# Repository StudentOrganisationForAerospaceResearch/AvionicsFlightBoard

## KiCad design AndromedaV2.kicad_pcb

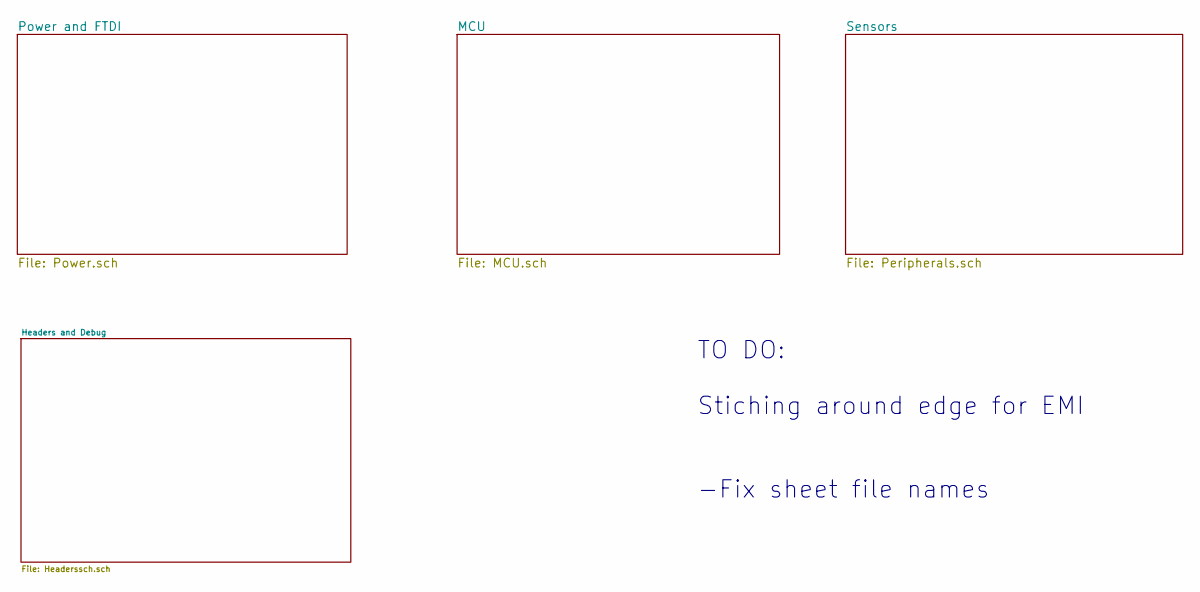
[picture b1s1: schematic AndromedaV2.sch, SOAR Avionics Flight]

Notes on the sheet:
TO DO: Stiching around edge for EMI -Fix sheet file names

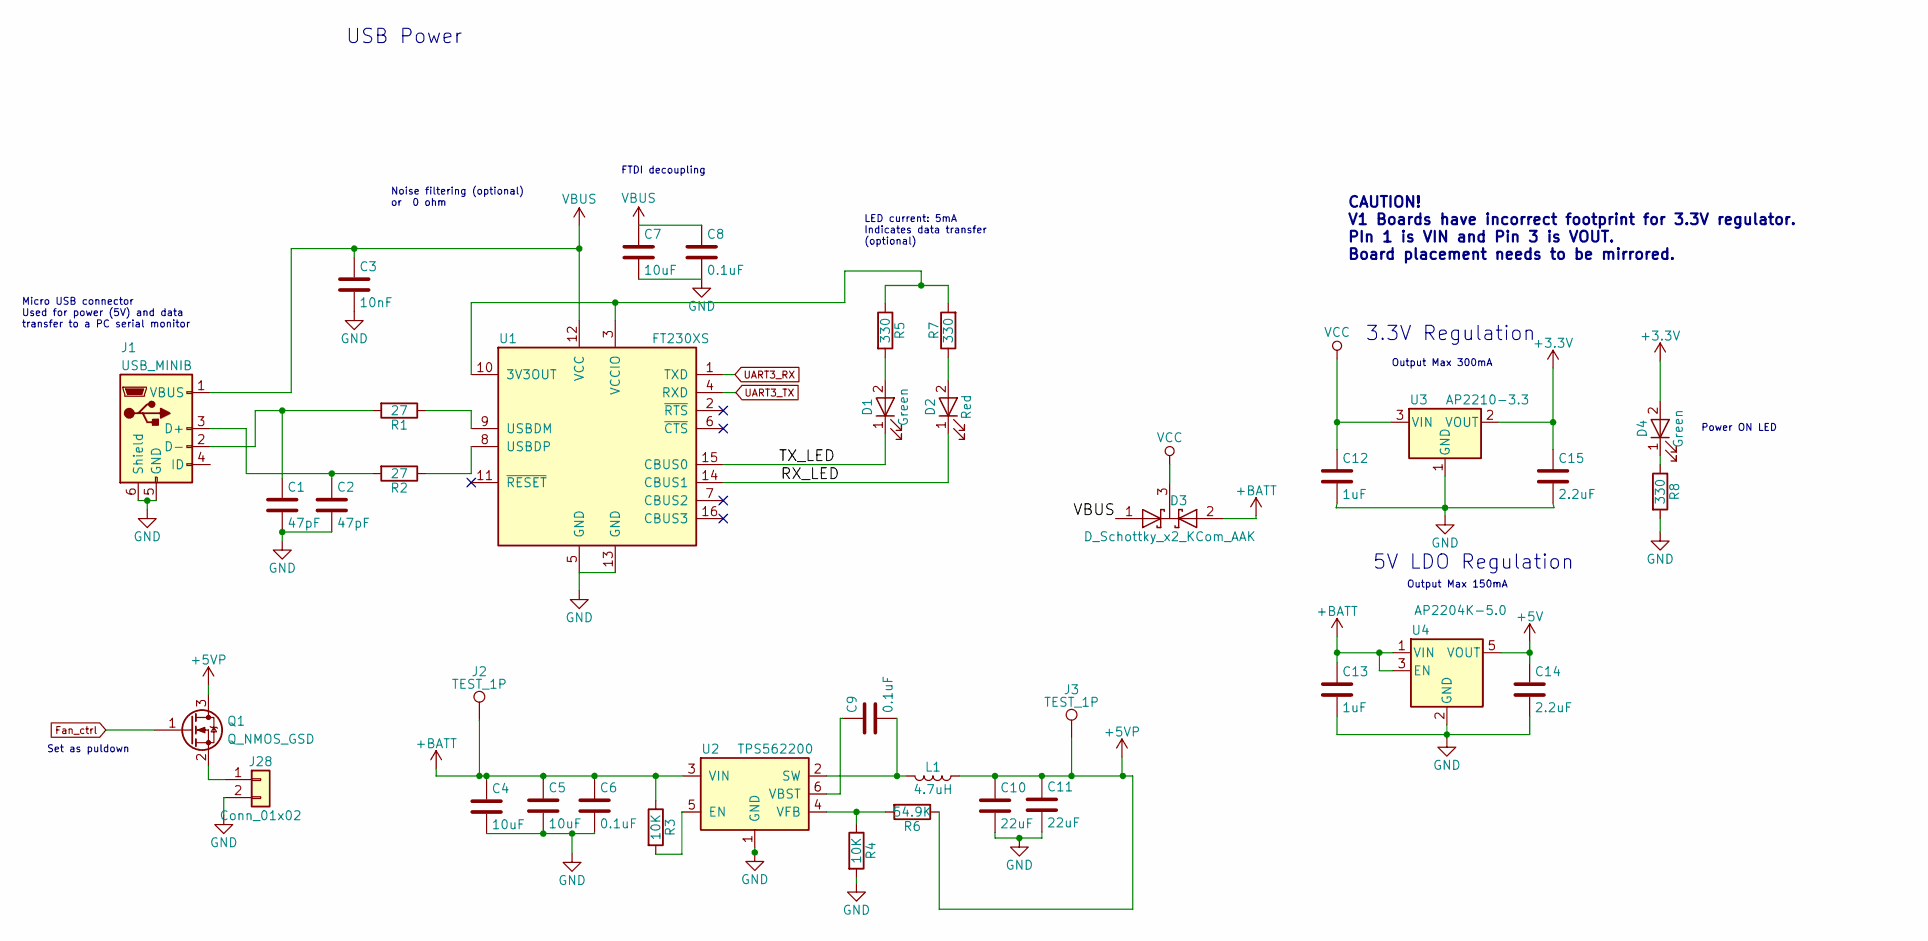
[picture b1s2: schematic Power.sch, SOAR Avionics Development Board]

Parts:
C1, C2: 47pF; C_0603
C3: 10nF; C_0603
C4, C5, C7: 10uF; C_0603
C6, C8, C9: 0.1uF; C_0603
C10, C11: 22uF; C_0603
C12, C13: 1uF; C_0603
C14, C15: 2.2uF; C_0603
D1, D4: Green; LED_0805_2012Metric; Digikey LG R971-KN-1
D2: Red; LED_0805_2012Metric; Digikey 475-1278-1-ND
D3: D_Schottky_x2_KCom_AAK; SOT-23; Digikey 1727-5188-1-ND
J1: USB_MINIB; USB-Mini-B; Digikey 690-005-299-043
J2, J3: TEST_1P; Test_Point_Pad_d1.5mm
J28: Conn_01x02; TerminalBlock_5mm_2POS_ED2600
L1: 4.7uH; L_1008
Q1: Q_NMOS_GSD; SOT-23
R1, R2: 27; R_0603
R3, R4: 10K; R_0603
R5, R7, R8: 330; R_0603
R6: 54.9K; R_0603
U1: FT230XS; SSOP-16_3.9x4.9mm_P0.635mm; Digikey 768-1135-1-ND
U2: TPS562200; SOT-23-6
U3: AP2210-3.3; SOT-23
U4: AP2204K-5.0; SOT-23-5

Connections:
+3V3: C15.1, D4.2 (A), U3.2 (VOUT); also elsewhere on the board
+5V: C14.1, U4.5 (VOUT); also elsewhere on the board
+5VP: C10.1, C11.1, J3.1, L1.1, Q1.3 (D), R6.1; also elsewhere on the board
+BATT: C4.1, C5.1, C6.1, C13.1, D3.2 (A), J2.1, R3.1, U2.3 (VIN), U4.1 (VIN), U4.3 (EN); also elsewhere on the board
/Power and FTDI/RX_LED: D2.1 (K), U1.14 (CBUS1)
/Power and FTDI/TX_LED: D1.1 (K), U1.15 (CBUS0)
Fan_ctrl: Q1.1 (G); also elsewhere on the board
GND: C1.2, C2.2, C3.2, C4.2, C5.2, C6.2, C7.2, C8.2, C10.2, C11.2, C12.2, C13.2, C14.2, C15.2, J1.5 (GND), J1.6 (Shield), J28.2, R4.2, R8.2, U1.5 (GND), U1.13 (GND), U2.1 (GND), U3.1 (GND), U4.2 (GND); also elsewhere on the board
unnamed: C1.1, J1.2 (D-), R1.2
unnamed: C2.1, J1.3 (D+), R2.2
unnamed: C9.1, U2.6 (VBST)
unnamed: C9.2, L1.2, U2.2 (SW)
unnamed: D1.2 (A), R5.2
unnamed: D2.2 (A), R7.1
unnamed: D4.1 (K), R8.1
unnamed: J28.1, Q1.2 (S)
unnamed: R1.1, U1.9 (USBDM)
unnamed: R2.1, U1.8 (USBDP)
unnamed: R3.2, U2.5 (EN)
unnamed: R4.1, R6.2, U2.4 (VFB)
unnamed: R5.1, R7.2
unnamed: U1.3 (VCCIO), U1.10 (3V3OUT)
UART3_RX: U1.1 (TXD); also elsewhere on the board
UART3_TX: U1.4 (RXD); also elsewhere on the board
VBUS: C3.1, C7.1, C8.1, D3.1 (A), J1.1 (VBUS), U1.12 (VCC)
VCC: C12.1, D3.3 (K), U3.3 (VIN)

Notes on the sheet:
Output Max 300mA
Power ON LED
LED current: 5mA Indicates data transfer (optional)
Micro USB connector Used for power (5V) and data transfer to a PC serial monitor
Noise filtering (optional) or 0 ohm
FTDI decoupling
USB Power
3.3V Regulation
5V LDO Regulation
CAUTION! V1 Boards have incorrect footprint for 3.3V regulator. PIn 1 is VIN and Pin 3 is VOUT. Board placement needs to be mirrored.
Output Max 150mA
Set as puldown

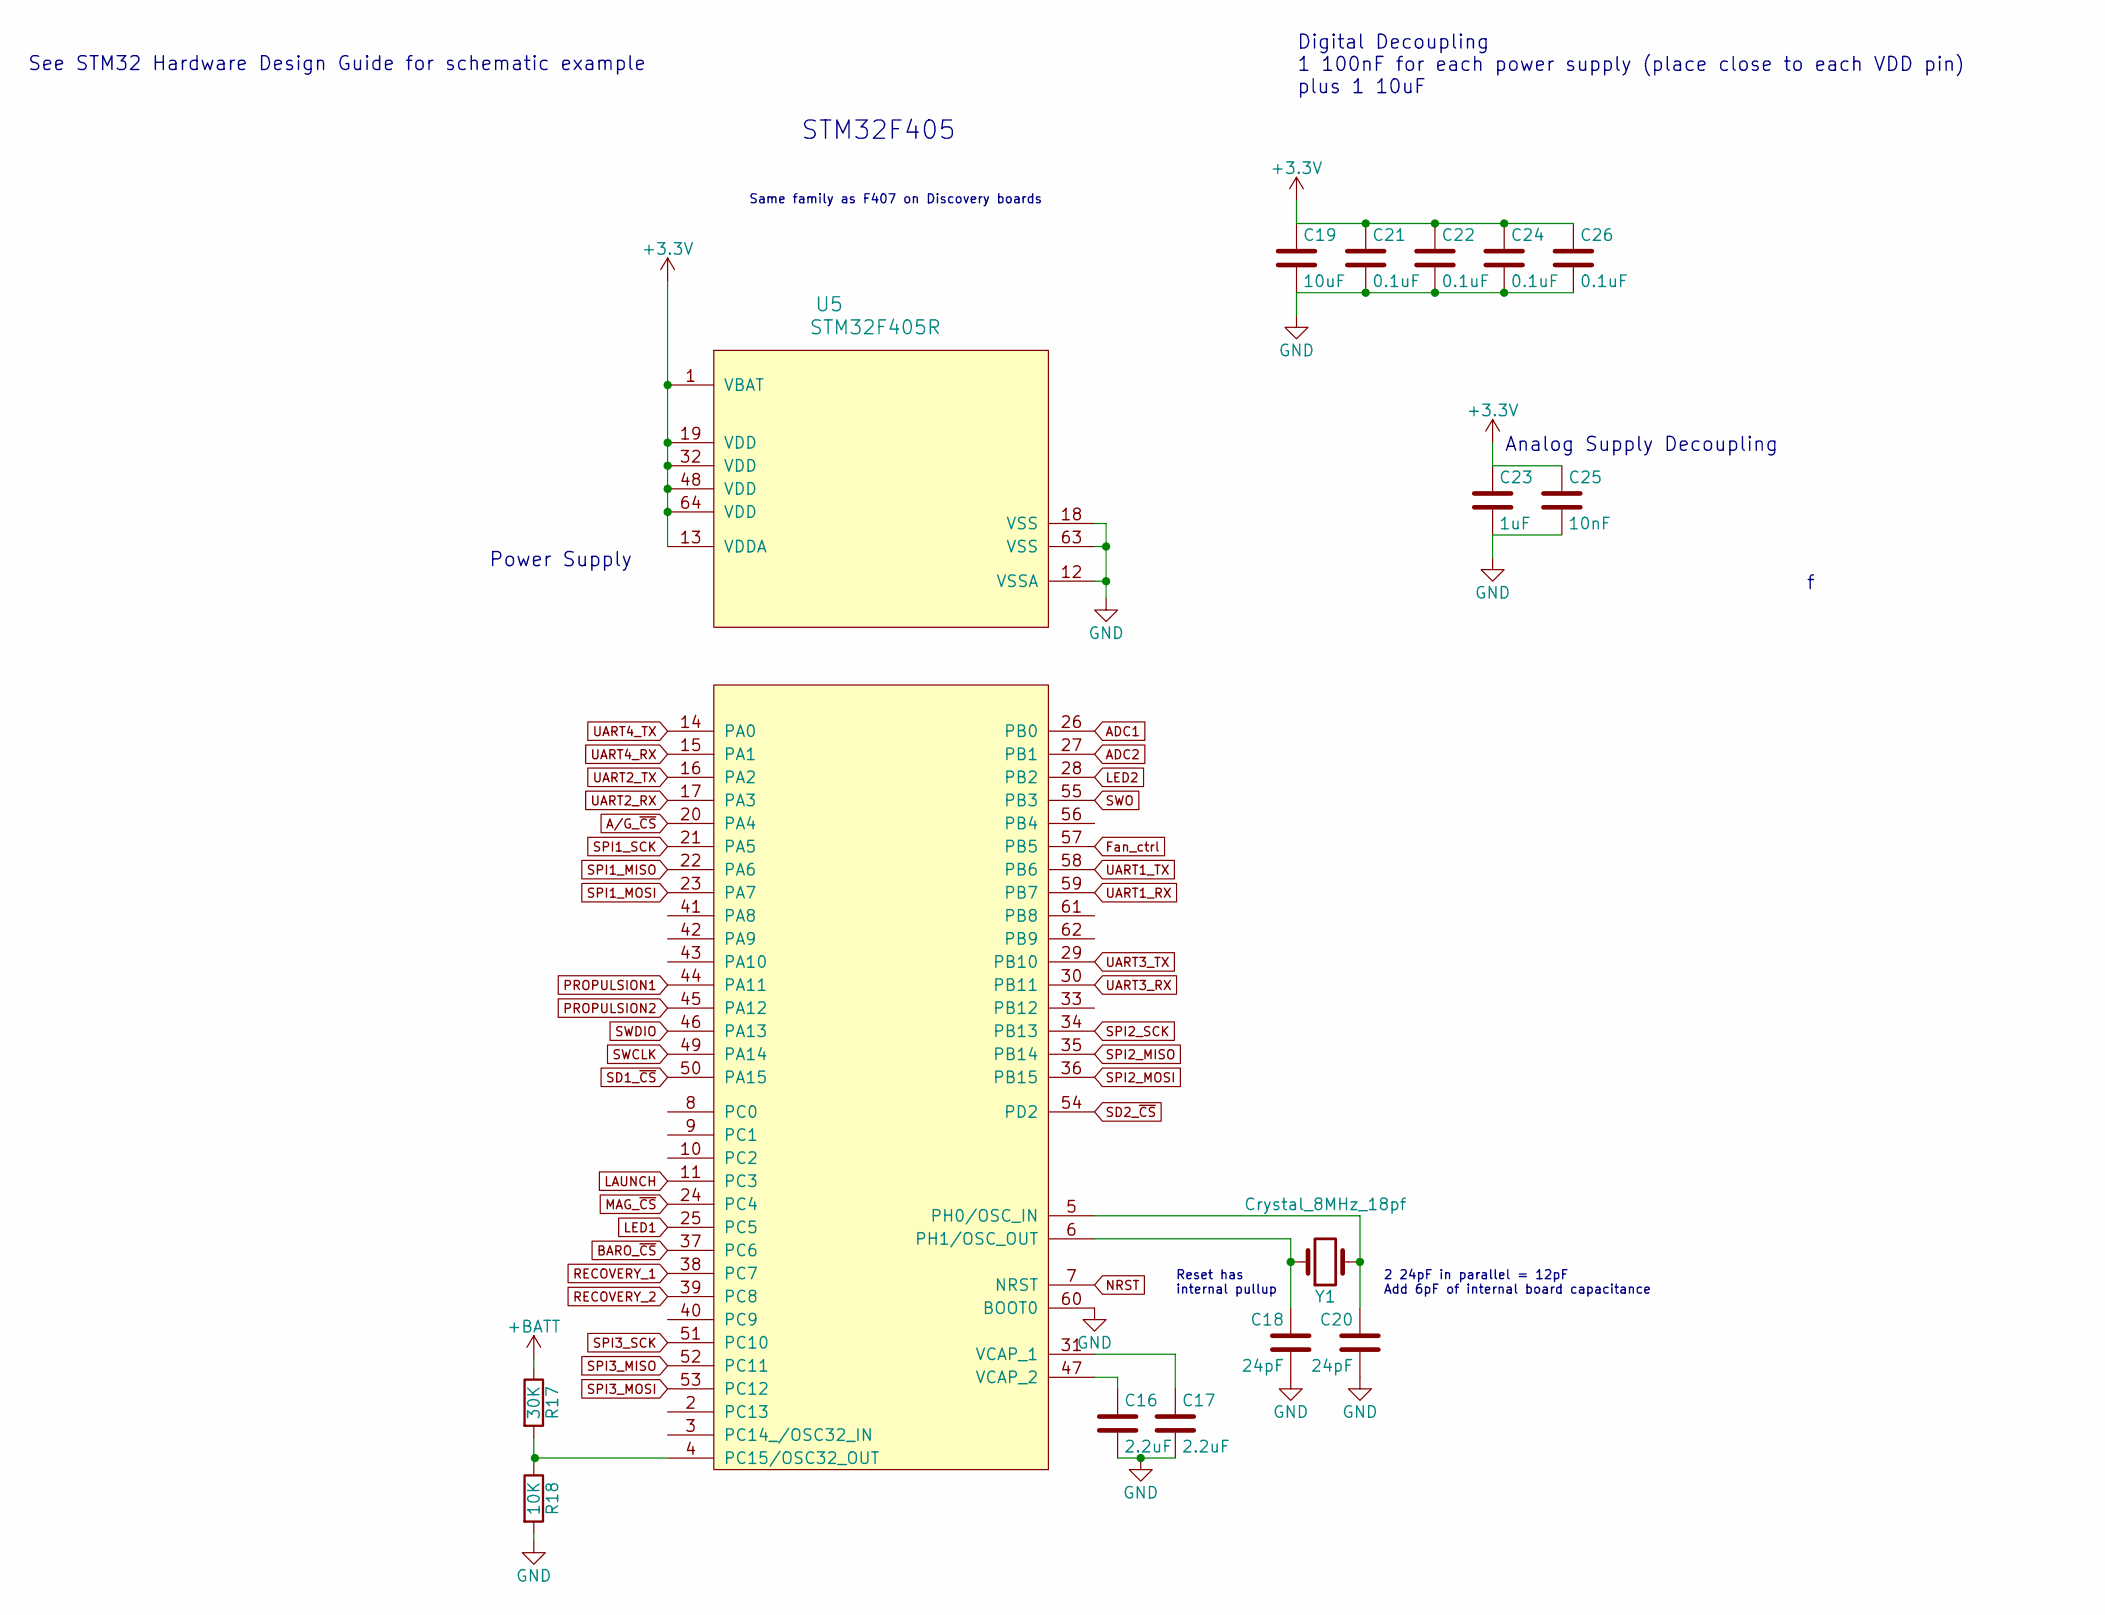
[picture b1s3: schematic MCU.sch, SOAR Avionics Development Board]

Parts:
C16, C17: 2.2uF; C_0603
C18, C20: 24pF; C_0603
C19: 10uF; C_0603
C21, C22, C24, C26: 0.1uF; C_0603
C23: 1uF; C_0603
C25: 10nF; C_0603
R17: 30K; R_0603
R18: 10K; R_0603
U5: STM32F405R; LQFP-64_10x10mm_P0.5mm; Digikey 497-11767-ND
Y1: Crystal_8MHz_18pf; Crystal_SMD_HC49-SD; Digikey 535-9089-1-ND

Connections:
+3V3: C19.1, C21.1, C22.1, C23.1, C24.1, C25.1, C26.1, U5.1 (VBAT), U5.13 (VDDA), U5.19 (VDD), U5.32 (VDD), U5.48 (VDD), U5.64 (VDD); also elsewhere on the board
+BATT: R17.1; also elsewhere on the board
A/G_~CS: U5.20 (PA4); also elsewhere on the board
ADC1: U5.26 (PB0); also elsewhere on the board
ADC2: U5.27 (PB1); also elsewhere on the board
BARO_~CS: U5.37 (PC6); also elsewhere on the board
Fan_ctrl: U5.57 (PB5); also elsewhere on the board
GND: C16.2, C17.2, C18.2, C19.2, C20.2, C21.2, C22.2, C23.2, C24.2, C25.2, C26.2, R18.2, U5.12 (VSSA), U5.18 (VSS), U5.60 (BOOT0), U5.63 (VSS); also elsewhere on the board
LAUNCH: U5.11 (PC3); also elsewhere on the board
LED1: U5.25 (PC5); also elsewhere on the board
LED2: U5.28 (PB2); also elsewhere on the board
MAG_~CS: U5.24 (PC4); also elsewhere on the board
NRST: U5.7 (NRST); also elsewhere on the board
unnamed: C16.1, U5.47 (VCAP_2)
unnamed: C17.1, U5.31 (VCAP_1)
unnamed: C18.1, U5.6 (PH1/OSC_OUT), Y1.1
unnamed: C20.1, U5.5 (PH0/OSC_IN), Y1.2
unnamed: R17.2, R18.1, U5.4 (PC15/OSC32_OUT)
PROPULSION1: U5.44 (PA11); also elsewhere on the board
PROPULSION2: U5.45 (PA12); also elsewhere on the board
RECOVERY_1: U5.38 (PC7); also elsewhere on the board
RECOVERY_2: U5.39 (PC8); also elsewhere on the board
SD1_~CS: U5.50 (PA15); also elsewhere on the board
SD2_~CS: U5.54 (PD2); also elsewhere on the board
SPI1_MISO: U5.22 (PA6); also elsewhere on the board
SPI1_MOSI: U5.23 (PA7); also elsewhere on the board
SPI1_SCK: U5.21 (PA5); also elsewhere on the board
SPI2_MISO: U5.35 (PB14); also elsewhere on the board
SPI2_MOSI: U5.36 (PB15); also elsewhere on the board
SPI2_SCK: U5.34 (PB13); also elsewhere on the board
SPI3_MISO: U5.52 (PC11); also elsewhere on the board
SPI3_MOSI: U5.53 (PC12); also elsewhere on the board
SPI3_SCK: U5.51 (PC10); also elsewhere on the board
SWCLK: U5.49 (PA14); also elsewhere on the board
SWDIO: U5.46 (PA13); also elsewhere on the board
SWO: U5.55 (PB3); also elsewhere on the board
UART1_RX: U5.59 (PB7); also elsewhere on the board
UART1_TX: U5.58 (PB6); also elsewhere on the board
UART2_RX: U5.17 (PA3); also elsewhere on the board
UART2_TX: U5.16 (PA2); also elsewhere on the board
UART3_RX: U5.30 (PB11); also elsewhere on the board
UART3_TX: U5.29 (PB10); also elsewhere on the board
UART4_RX: U5.15 (PA1); also elsewhere on the board
UART4_TX: U5.14 (PA0); also elsewhere on the board

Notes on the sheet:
Reset has internal pullup
Digital Decoupling 1 100nF for each power supply (place close to each VDD pin) plus 1 10uF
Analog Supply Decoupling
See STM32 Hardware Design Guide for schematic example
Power Supply
2 24pF in parallel = 12pF Add 6pF of internal board capacitance
STM32F405
Same family as F407 on Discovery boards

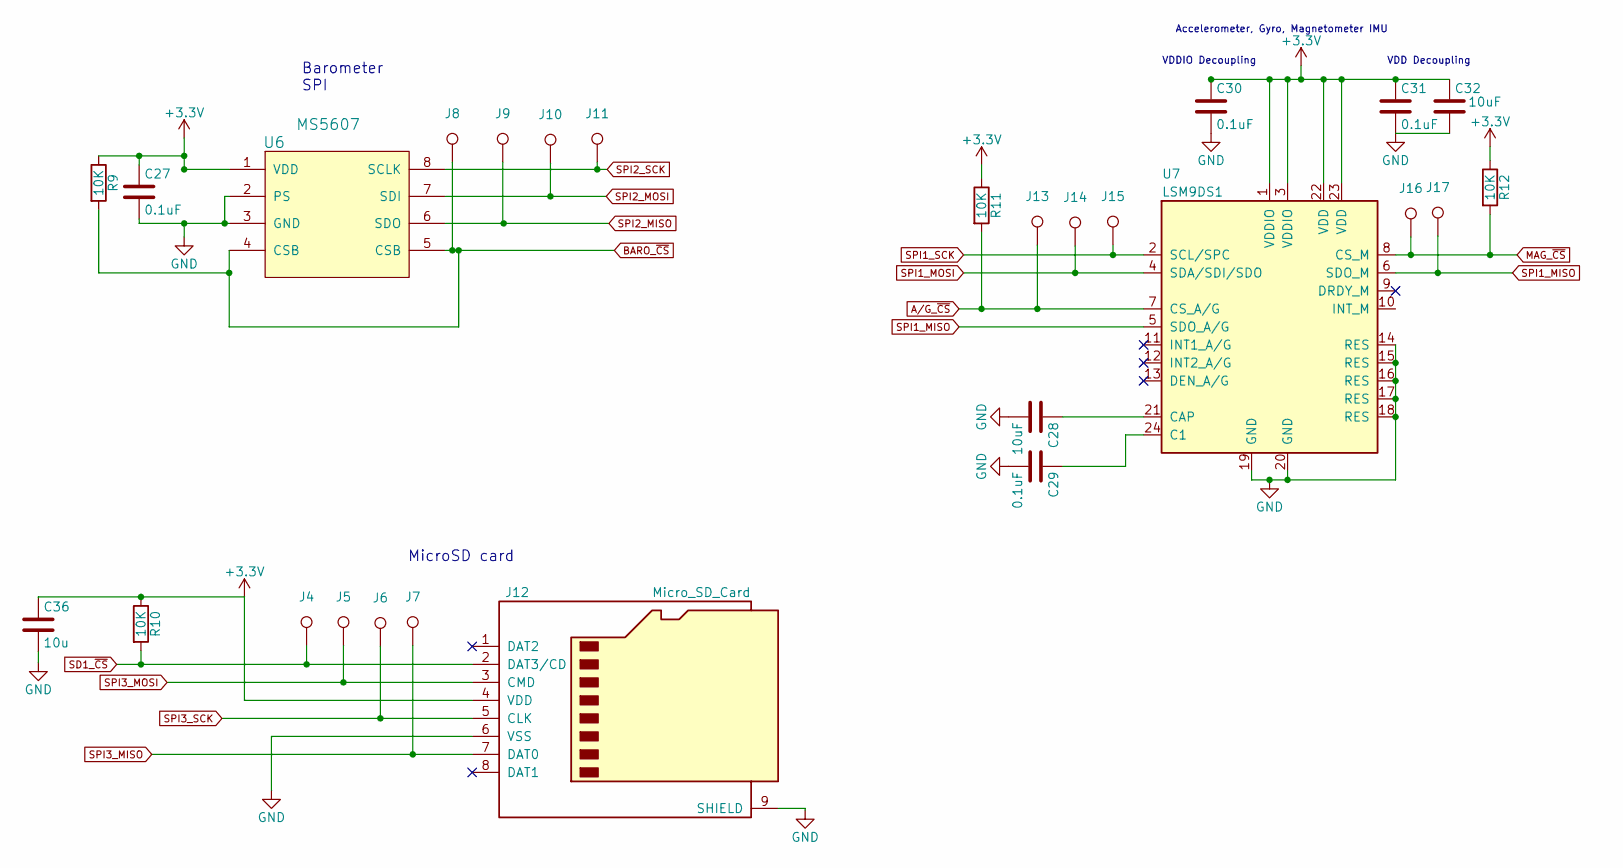
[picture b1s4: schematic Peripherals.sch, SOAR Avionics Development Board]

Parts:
C27, C29, C30, C31: 0.1uF; C_0603
C28, C32: 10uF; C_0603
C36: 10u; C_0603
J4, J5, J6, J7, J8, J9, J10, J11, J13, J14, J15, J16, J17: TEST_1P; Test_Point_Pad_d1.5mm
J12: Micro_SD_Card; Conn,Molex,Hinged_microSD; Digikey 0472192001
R9, R10, R11, R12: 10K; R_0603
U6: MS5607; LGA-8_3x5mm_P1.25mm; Digikey MS560702BA03-00
U7: LSM9DS1; LGA-24L_3x3.5mm_P0.43mm; Digikey 497-14946-1-ND

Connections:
+3V3: C27.1, C30.1, C31.1, C32.1, C36.1, J12.4 (VDD), R9.1, R10.1, R11.1, R12.1, U6.1 (VDD), U7.1 (VDDIO), U7.3 (VDDIO), U7.22 (VDD), U7.23 (VDD); also elsewhere on the board
A/G_~CS: J13.1, R11.2, U7.7 (CS_A/G); also elsewhere on the board
BARO_~CS: J8.1, R9.2, U6.4 (CSB), U6.5 (CSB); also elsewhere on the board
GND: C27.2, C28.2, C29.2, C30.2, C31.2, C32.2, C36.2, J12.6 (VSS), J12.9 (SHIELD), U6.2 (PS), U6.3 (GND), U7.14 (RES), U7.15 (RES), U7.16 (RES), U7.17 (RES), U7.18 (RES), U7.19 (GND), U7.20 (GND); also elsewhere on the board
MAG_~CS: J16.1, R12.2, U7.8 (CS_M); also elsewhere on the board
unnamed: C28.1, U7.21 (CAP)
unnamed: C29.1, U7.24 (C1)
SD1_~CS: J4.1, J12.2 (DAT3/CD), R10.2; also elsewhere on the board
SPI1_MISO: J17.1, U7.5 (SDO_A/G), U7.6 (SDO_M); also elsewhere on the board
SPI1_MOSI: J14.1, U7.4 (SDA/SDI/SDO); also elsewhere on the board
SPI1_SCK: J15.1, U7.2 (SCL/SPC); also elsewhere on the board
SPI2_MISO: J9.1, U6.6 (SDO); also elsewhere on the board
SPI2_MOSI: J10.1, U6.7 (SDI); also elsewhere on the board
SPI2_SCK: J11.1, U6.8 (SCLK); also elsewhere on the board
SPI3_MISO: J7.1, J12.7 (DAT0); also elsewhere on the board
SPI3_MOSI: J5.1, J12.3 (CMD); also elsewhere on the board
SPI3_SCK: J6.1, J12.5 (CLK); also elsewhere on the board

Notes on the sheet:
Barometer SPI
VDD Decoupling
VDDIO Decoupling
MicroSD card
Accelerometer, Gyro, Magnetometer IMU

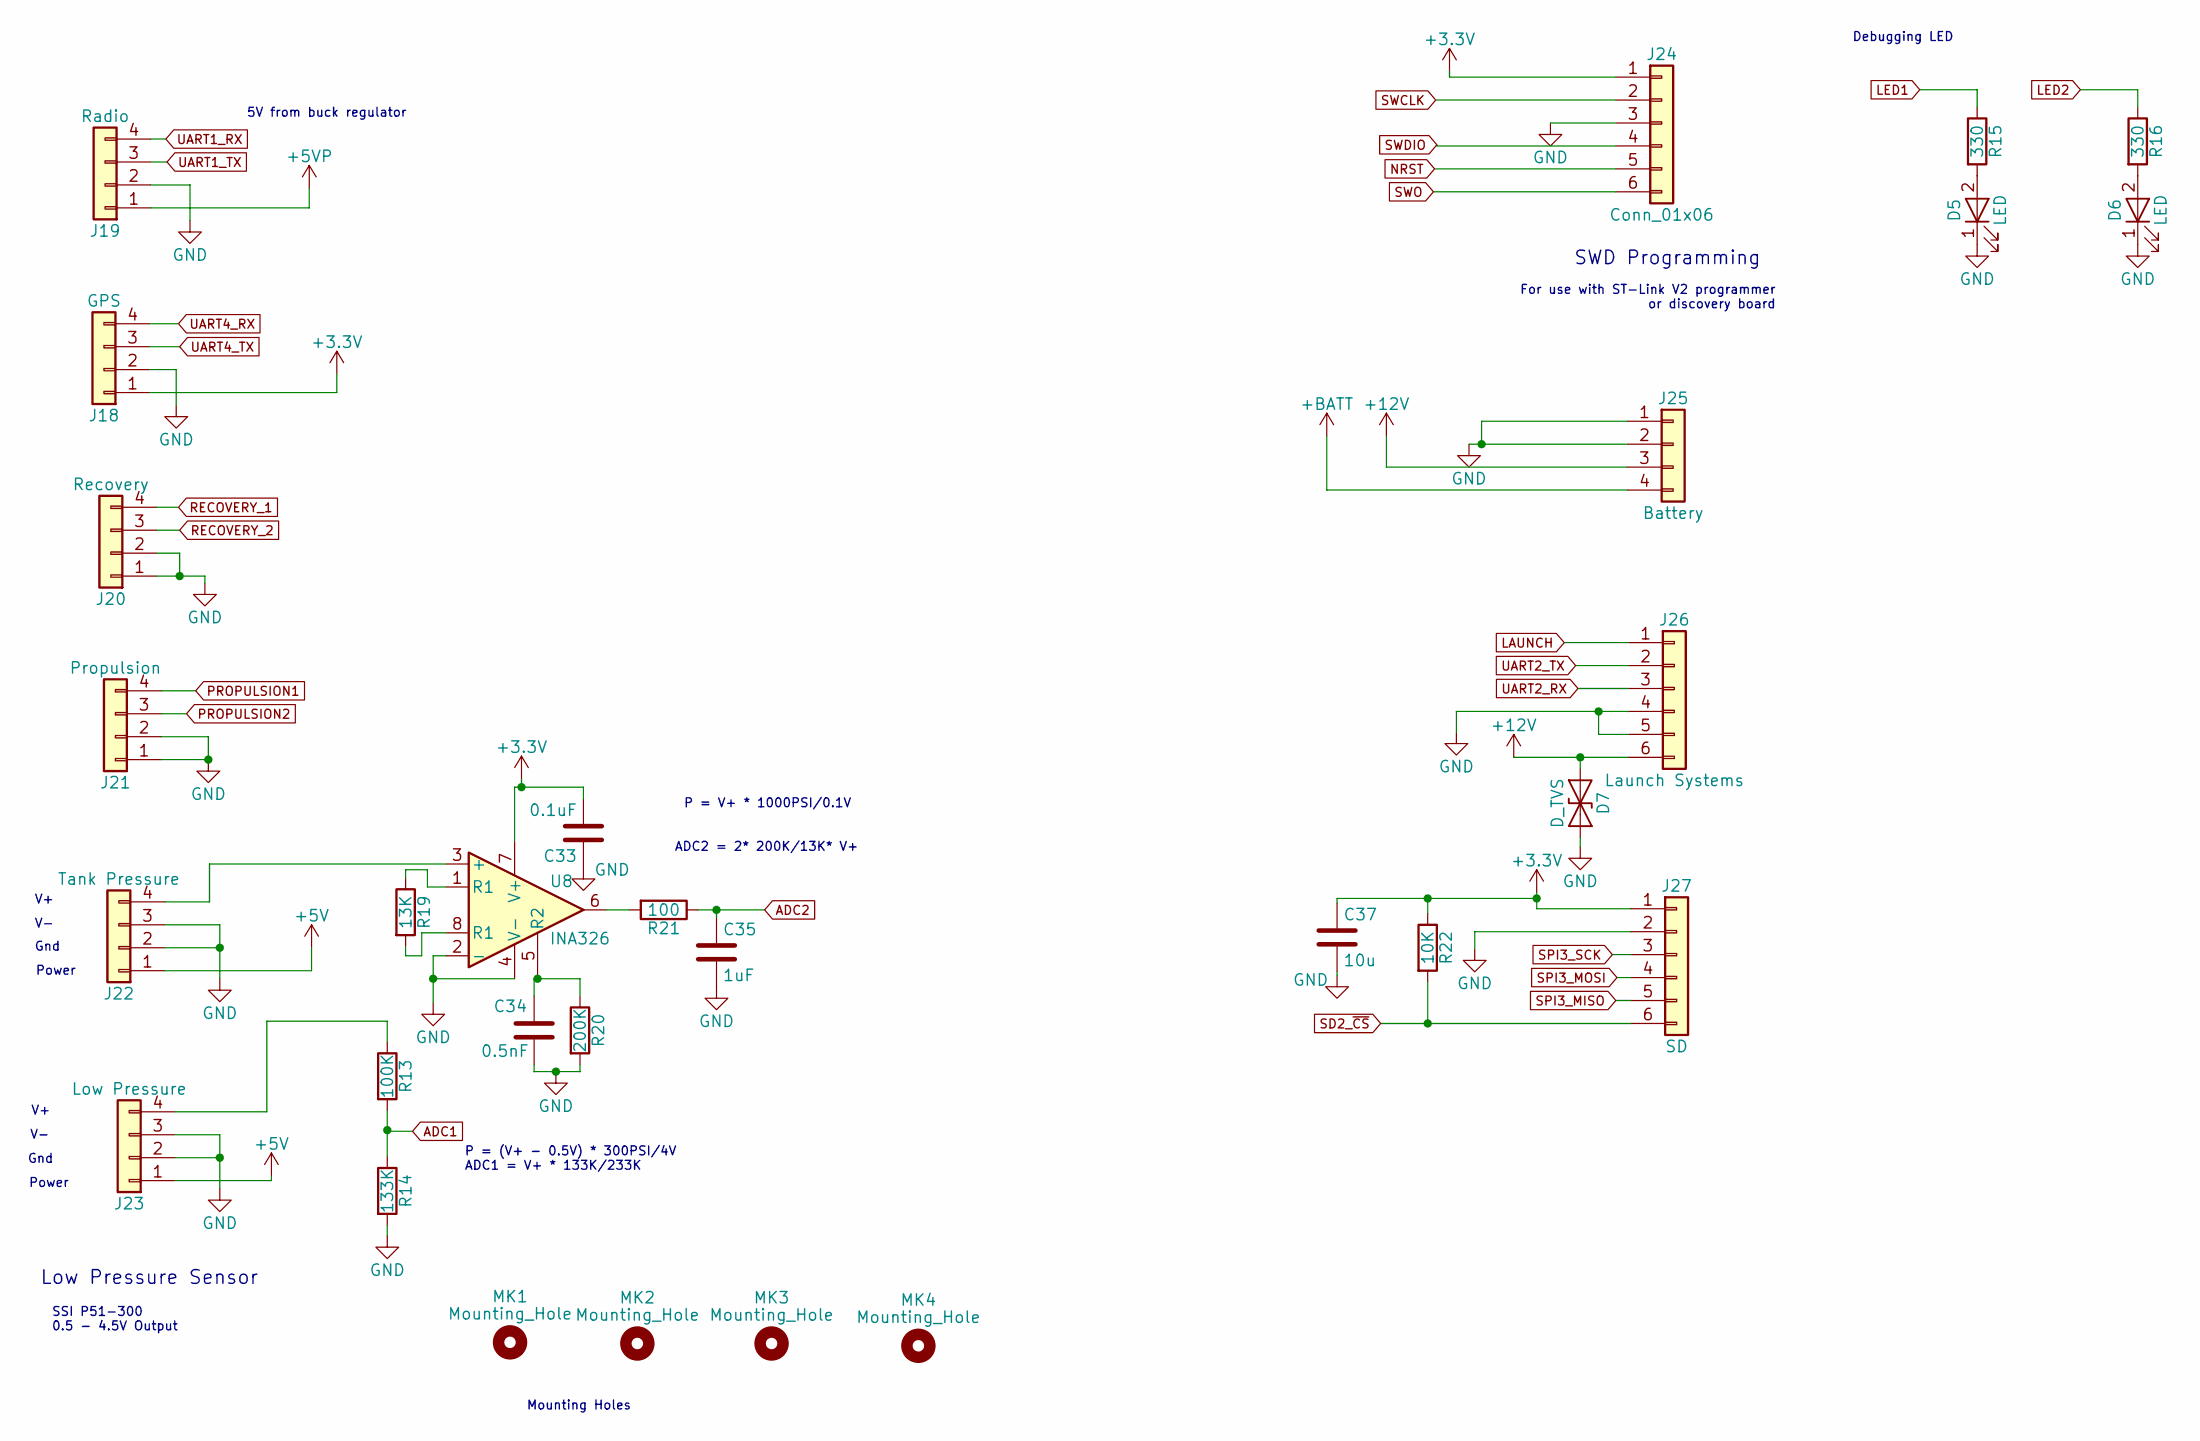
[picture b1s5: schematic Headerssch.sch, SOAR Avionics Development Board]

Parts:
C33: 0.1uF; C_0603
C34: 0.5nF; C_0603
C35: 1uF; C_0603
C37: 10u; C_0603
D5, D6: LED; LED_0805_2012Metric
D7: D_TVS; D_SOD-323
J18: GPS; Molex_Micro-Fit_3.0_43045-0400_2x02_P3.00mm_Horizontal
J19: Radio; Molex_Micro-Fit_3.0_43045-0400_2x02_P3.00mm_Horizontal
J20: Recovery; Molex_Micro-Fit_3.0_43045-0400_2x02_P3.00mm_Horizontal
J21: Propulsion; Molex_Micro-Fit_3.0_43045-0400_2x02_P3.00mm_Horizontal
J22: Tank Pressure; Molex_Micro-Fit_3.0_43045-0400_2x02_P3.00mm_Horizontal
J23: Low Pressure; Molex_Micro-Fit_3.0_43045-0400_2x02_P3.00mm_Horizontal
J24: Conn_01x06; PinHeader_1x06_P2.54mm_Vertical
J25: Battery; Molex_Micro-Fit_3.0_43045-0400_2x02_P3.00mm_Horizontal
J26: Launch Systems; Molex_Micro-Fit_3.0_43045-0600_2x03_P3.00mm_Horizontal
J27: SD; Molex_Micro-Fit_3.0_43045-0600_2x03_P3.00mm_Horizontal
MK1, MK2, MK3, MK4: Mounting_Hole; MountingHole_3.2mm_M3
R13: 100K; R_0603
R14: 133K; R_0603
R15, R16: 330; R_0603
R19: 13K; R_0603
R20: 200K; R_0603
R21: 100; R_0603
R22: 10K; R_0603
U8: INA326; MSOP-8_3x3mm_Pitch0.65mm

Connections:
+3V3: C33.2, C37.1, J18.1, J24.1, J27.1, R22.1, U8.7 (V+); also elsewhere on the board
+5V: J22.1, J23.1; also elsewhere on the board
+5VP: J19.1; also elsewhere on the board
+12V: D7.1 (A1), J25.3, J26.6
+BATT: J25.4; also elsewhere on the board
ADC1: R13.2, R14.1; also elsewhere on the board
ADC2: C35.1, R21.1; also elsewhere on the board
GND: C33.1, C34.2, C35.2, C37.2, D5.1 (K), D6.1 (K), D7.2 (A2), J18.2, J19.2, J20.1, J20.2, J21.1, J21.2, J22.2, J22.3, J23.2, J23.3, J24.3, J25.1, J25.2, J26.4, J26.5, J27.2, R14.2, R20.2, U8.2 (-), U8.4 (V-); also elsewhere on the board
LAUNCH: J26.1; also elsewhere on the board
LED1: R15.1; also elsewhere on the board
LED2: R16.1; also elsewhere on the board
NRST: J24.5; also elsewhere on the board
unnamed: C34.1, R20.1, U8.5 (R2)
unnamed: D5.2 (A), R15.2
unnamed: D6.2 (A), R16.2
unnamed: J22.4, U8.3 (+)
unnamed: J23.4, R13.1
unnamed: R19.1, U8.1 (R1)
unnamed: R19.2, U8.8 (R1)
unnamed: R21.2, U8.6
PROPULSION1: J21.4; also elsewhere on the board
PROPULSION2: J21.3; also elsewhere on the board
RECOVERY_1: J20.4; also elsewhere on the board
RECOVERY_2: J20.3; also elsewhere on the board
SD2_~CS: J27.6, R22.2; also elsewhere on the board
SPI3_MISO: J27.5; also elsewhere on the board
SPI3_MOSI: J27.4; also elsewhere on the board
SPI3_SCK: J27.3; also elsewhere on the board
SWCLK: J24.2; also elsewhere on the board
SWDIO: J24.4; also elsewhere on the board
SWO: J24.6; also elsewhere on the board
UART1_RX: J19.4; also elsewhere on the board
UART1_TX: J19.3; also elsewhere on the board
UART2_RX: J26.3; also elsewhere on the board
UART2_TX: J26.2; also elsewhere on the board
UART4_RX: J18.4; also elsewhere on the board
UART4_TX: J18.3; also elsewhere on the board

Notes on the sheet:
SWD Programming
For use with ST-Link V2 programmer or discovery board
Debugging LED
Mounting Holes
Low Pressure Sensor
Power
Gnd
5V from buck regulator
SSI P51-300 0.5 - 4.5V Output
P = (V+ - 0.5V) * 300PSI/4V ADC1 = V+ * 133K/233K
ADC2 = 2* 200K/13K* V+
P = V+ * 1000PSI/0.1V

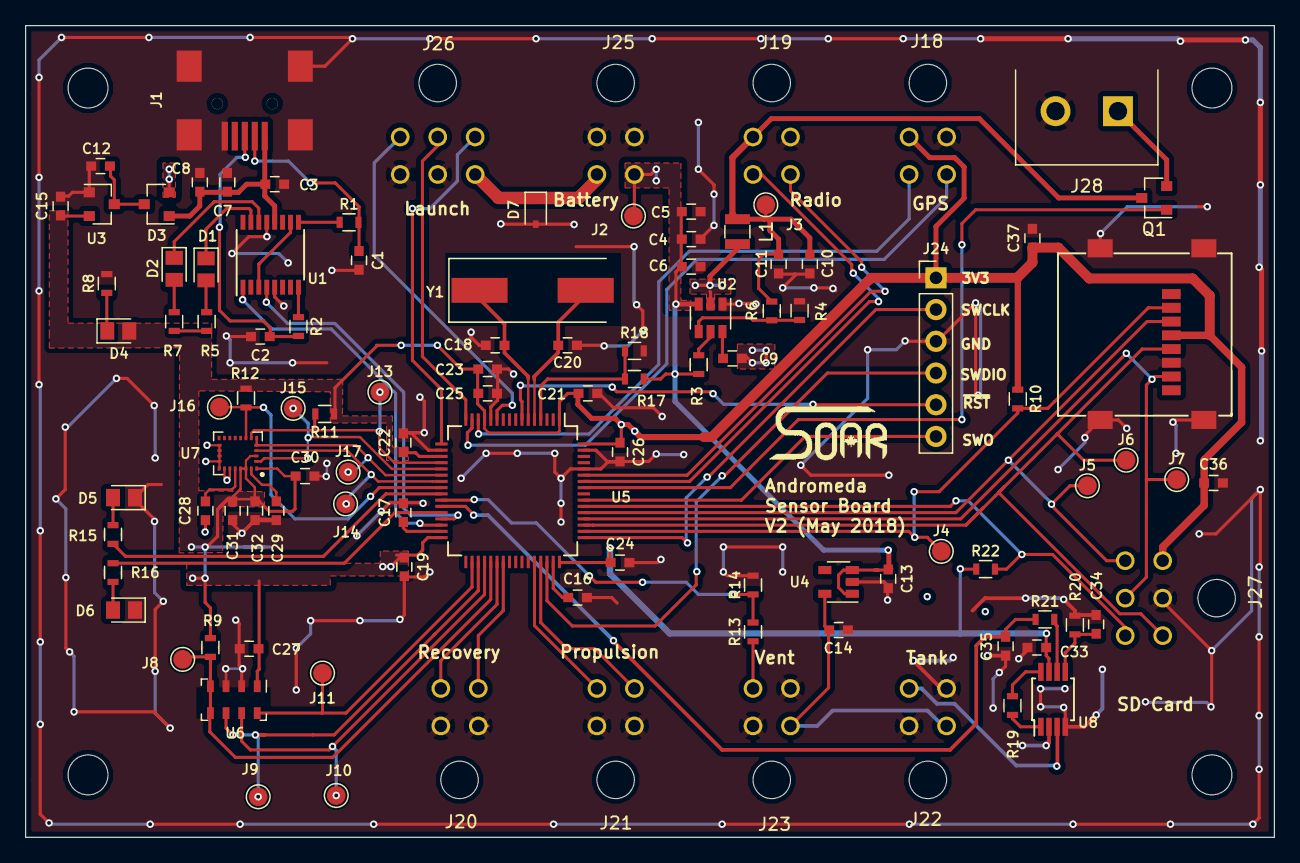
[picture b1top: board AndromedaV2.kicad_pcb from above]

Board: 2 copper layers, 100.0 x 65.0 mm, 110 parts (0 on the bottom side), 75 nets.

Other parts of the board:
LOGO_SOAR: LOGO_SOAR

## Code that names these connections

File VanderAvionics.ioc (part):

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Mcu.Name=STM32F405RGTx
Mcu.Package=LQFP64
Mcu.UserName=STM32F405RGTx
PA0-WKUP.Mode=Asynchronous
PA0-WKUP.Signal=UART4_TX
PA1.Mode=Asynchronous
PA1.Signal=UART4_RX
PA11.GPIOParameters=GPIO_Label
PA11.GPIO_Label=PROPULSION1
PA11.Signal=GPIO_Output
PA12.GPIOParameters=GPIO_Label
PA12.GPIO_Label=PROPULSION2
PA12.Signal=GPIO_Output
PA13.Signal=SYS_JTMS-SWDIO
PA14.Signal=SYS_JTCK-SWCLK
PA15.GPIOParameters=GPIO_Label
PA15.GPIO_Label=SD2_CS'
PA15.Signal=GPIO_Output
PA2.Mode=Asynchronous
PA2.Signal=USART2_TX
PA3.Mode=Asynchronous
PA3.Signal=USART2_RX
PA4.GPIOParameters=GPIO_Label
PA4.GPIO_Label=A/G_CS'
PA4.Signal=GPIO_Output
PA5.Mode=Full_Duplex_Master
PA5.Signal=SPI1_SCK
PA6.Mode=Full_Duplex_Master
PA6.Signal=SPI1_MISO
PA7.Mode=Full_Duplex_Master
PA7.Signal=SPI1_MOSI
PB0.Signal=ADCx_IN8
PB1.Signal=ADCx_IN9
PB10.Mode=Asynchronous
PB10.Signal=USART3_TX
PB11.Mode=Asynchronous
PB11.Signal=USART3_RX
PB13.Mode=Full_Duplex_Master
PB13.Signal=SPI2_SCK
PB14.Mode=Full_Duplex_Master
PB14.Signal=SPI2_MISO
PB15.Mode=Full_Duplex_Master
PB15.Signal=SPI2_MOSI
PB2.GPIOParameters=GPIO_Label
PB2.GPIO_Label=LED2
PB2.Signal=GPIO_Output
PB3.Signal=SYS_JTDO-SWO
PB6.Mode=Asynchronous
PB6.Signal=USART1_TX
PB7.Mode=Asynchronous
PB7.Signal=USART1_RX
PC10.Mode=Full_Duplex_Master
PC10.Signal=SPI3_SCK
PC11.Mode=Full_Duplex_Master
PC11.Signal=SPI3_MISO
PC12.Mode=Full_Duplex_Master
PC12.Signal=SPI3_MOSI
PC3.GPIOParameters=GPIO_Label
PC3.GPIO_Label=Launch Systems
PC3.Signal=GPIO_Input
PC4.GPIOParameters=GPIO_Label
PC4.GPIO_Label=MAG_CS'
PC4.Signal=GPIO_Output
PC5.GPIOParameters=GPIO_Label
PC5.GPIO_Label=LED1
PC5.Signal=GPIO_Output
PC6.GPIOParameters=GPIO_Label
PC6.GPIO_Label=Baro_CS'
PC6.Signal=GPIO_Output
PC7.GPIOParameters=GPIO_Label
PC7.GPIO_Label=RECOVERY1
PC7.Signal=GPIO_Output
PC8.GPIOParameters=GPIO_Label
PC8.GPIO_Label=RECOVERY2
PC8.Signal=GPIO_Output
PD2.GPIOParameters=GPIO_Label
PD2.GPIO_Label=SD2_CS'
PD2.Signal=GPIO_Output
PH0-OSC_IN.Mode=HSE-External-Oscillator
PH0-OSC_IN.Signal=RCC_OSC_IN
PH1-OSC_OUT.Mode=HSE-External-Oscillator
PH1-OSC_OUT.Signal=RCC_OSC_OUT
RCC.HSE_VALUE=8000000
RCC.SYSCLKFreq_VALUE=168000000
RCC.SYSCLKSource=RCC_SYSCLKSOURCE_PLLCLK

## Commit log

2018-04-29 initial project commit
2018-04-29 Add schematic PDF
2018-05-05 add Terminal Block 5mm
2018-05-07 further work on schematic and PCB
2018-05-07 remove unnecessary files
2018-05-08 Bring schematic in line with PCB. Previous update broke this.
2018-05-08 Add schem documentation and generate new PDF
2018-05-11 Changes based on review reccommemdations
2018-05-17 Final design published. Gerbers and PDF schematic generated
